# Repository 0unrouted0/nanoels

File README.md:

This software and instructions are [provided as is](LICENSE), without warranty of any kind.

See [the data of kachurovskiy](https://github.com/kachurovskiy/nanoels/) for the original NanoEls

# NanoEls H4 revised1 (currently unfinished work!!)
* This is an idea of an low cost variant with multiple placement and handsolder types for the components. For e.g.
    * PCB double sided 100mm x 100mm standard type
    * Design with free KiCad 8
    * All parts for hand solder (TCA8418 tricky, but possible - or usage of Adafruit Module)
    * One PCB for keypad and controls
    * Powering over USB or step-down converter with screw terminals
    * Interfacing to LCD via I2C interface over 4 pins possible (== same LCD type with I2C backpack PCB as sold on Aliexpress)
    * USB program and serial interface variants FT232RL or CH340 series
    * USB Connectors 90° types in two sides (idea: back connector>power, front connector>PC-control) or side entry both over 180° Types
    * ESP32-S3-WROOM-1 also possible (with antenna), currently used N16R8

* What's working in Hardware (with modified software)?
	* WARNING: This special hardware version is not checked against EMC, CE, FCC and so on...
    * Display over I2C Interface
    * Programming and serial interface over FT232RL for the ESP32-S3-WROOM-1 (N16R8)
    * Keypad with direct soldered Keypad controller

* What's working in Software?
    * Software should be (i can not test it) compatible with the original NanoEls H4
    * Software working with ardunio Espressive ESP32 3.0.1 boards package (based on ESP-IDF v5.1.4). Maybe NOT backwards compatible to 2.x.
    * Display in I2C mode working. Faultless together with secondary I2C channel for keypad interface. 
    * Added LiquidCrystal_I2C_pt for handling of two I2C interfaces an changeable pins, because there are no available Arduino libraries with I2C pointer parameter.
    * Currently not completely tested, but encoder detects something. Hardware timer for ASYNC and A1 mode maybe not 100% working (unclear).

* ToDo's and current bugs
    * More testing of HW and SW
    * Integration in a real lathe
    * Making a low cost 3d-printable housing
    * PCB: Pitch of buzzer is false for the delivered type. Maybe a dual pitch package is sensible
    * PCB: Through hole pad for thermal connection of ESP32 module should have a bigger size free of solder mask
    * PCB: maybe dual package in standard sizes for buzzer free wheeling diode
    * PCB: upload the latest version

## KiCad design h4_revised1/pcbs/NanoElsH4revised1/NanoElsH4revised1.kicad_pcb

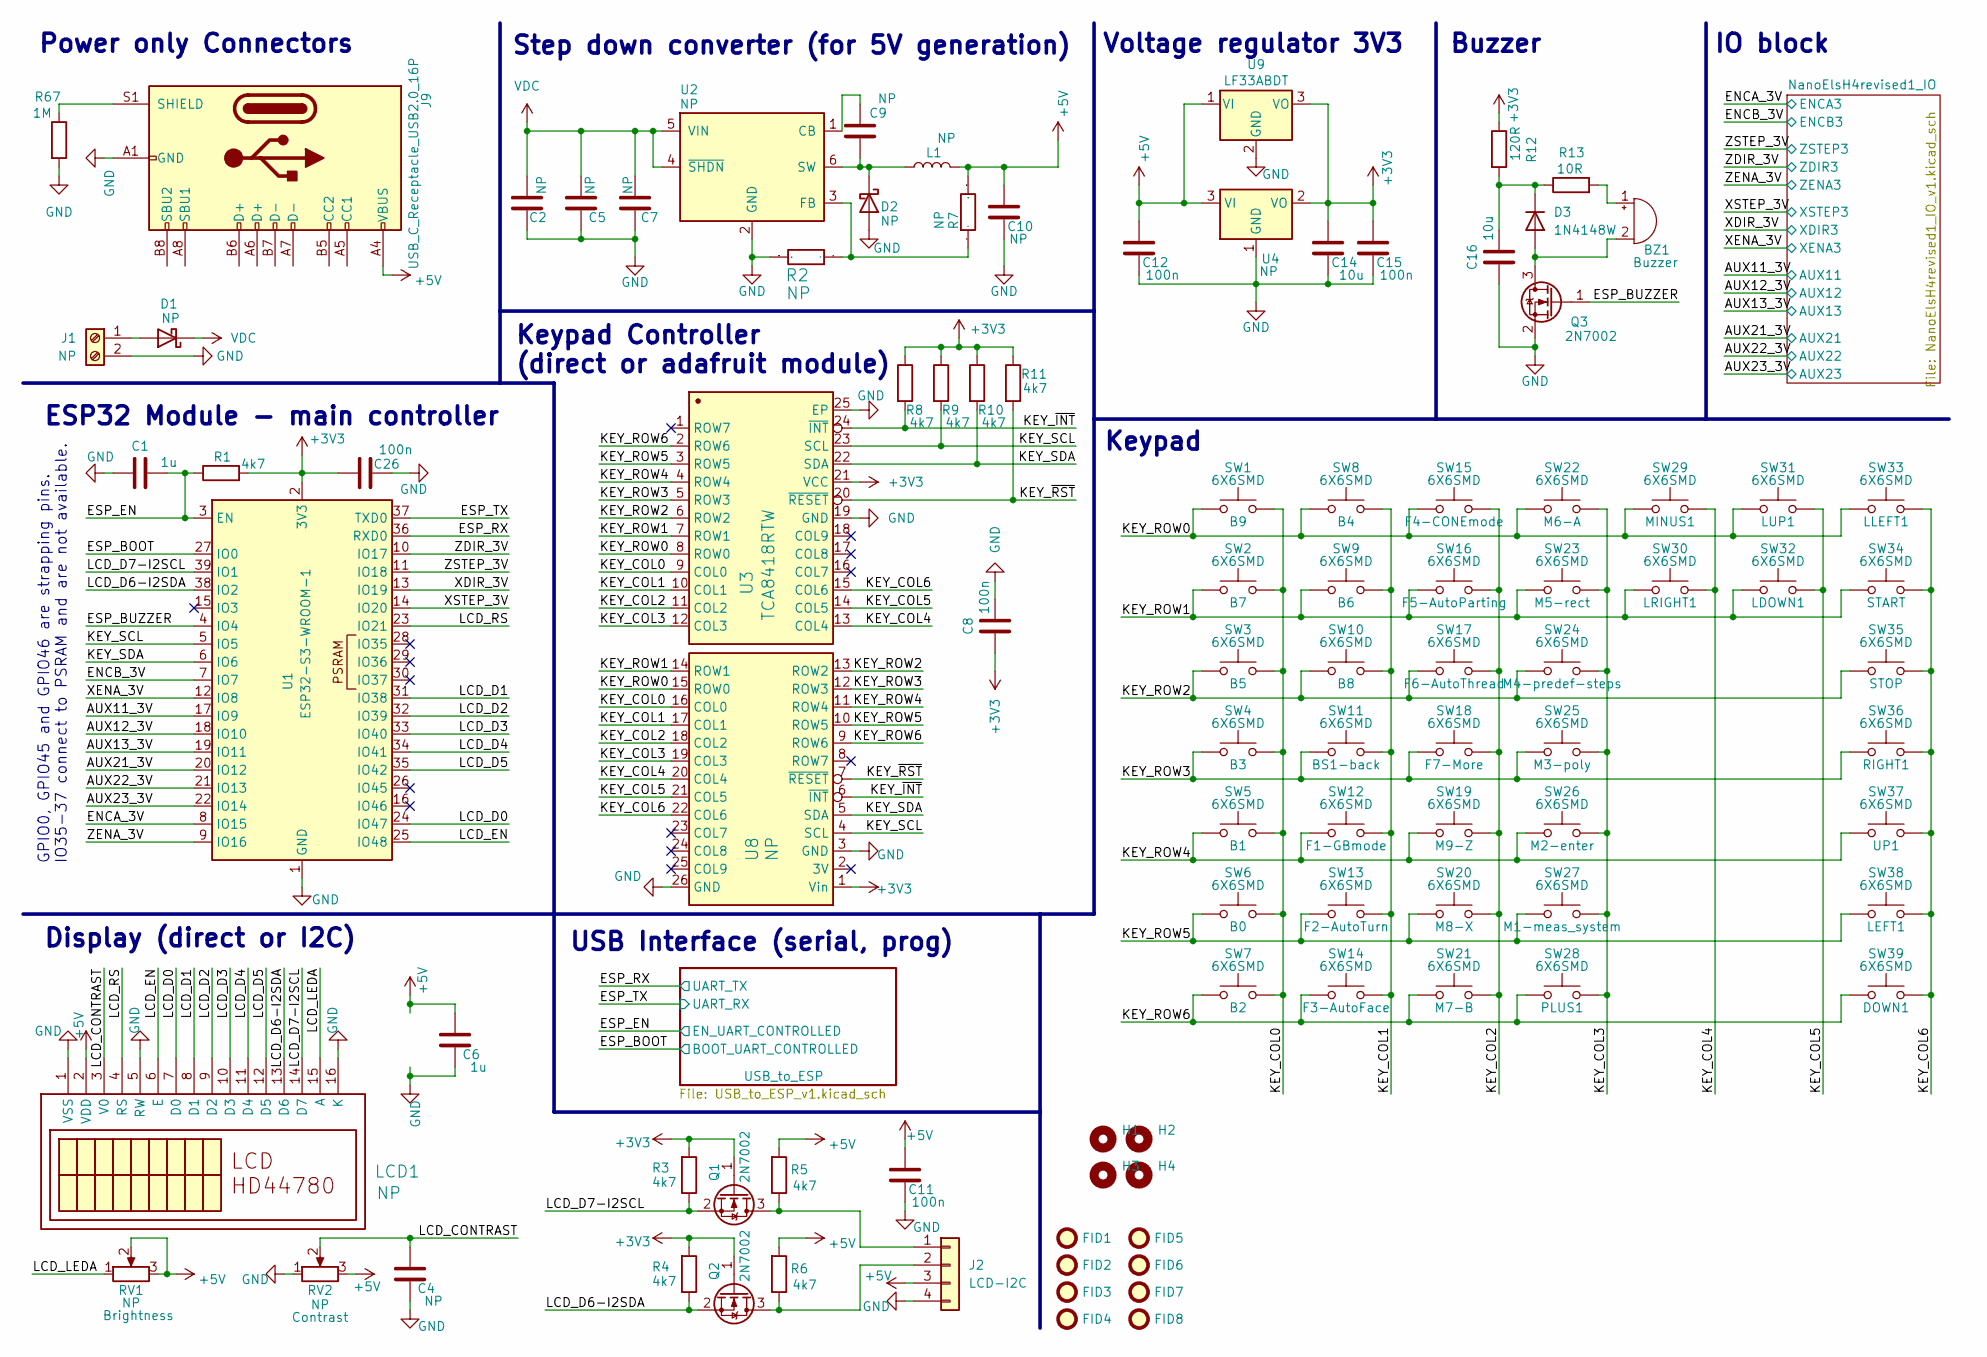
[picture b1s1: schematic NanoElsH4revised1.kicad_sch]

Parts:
BZ1: Buzzer; MagneticBuzzer_PUI_AT-0927-TT-6-R
C1, C6: 1u; C_0603_1608Metric
C2, C5: NP; C_1210_3225Metric
C4, C7, C9: NP; C_0603_1608Metric
C8, C11, C12, C15, C26: 100n; C_0603_1608Metric
C10: NP; C_1206_3216Metric
C14, C16: 10u; C_1206_3216Metric
D1, D2: NP; D_SMA
D3: 1N4148W; D_SOD-323
FID1, FID2, FID3, FID4, FID5, FID6, FID7, FID8: Fiducial_1.5mm_Mask3mm
H1, H2, H3, H4: MountingHole_3.2mm_M3
J1: NP; PhoenixContact_MCV_1,5_2-G-3.5_1x02_P3.50mm_Vertical
J2: LCD-I2C; PinHeader_1x04_P2.54mm_Horizontal
J9: USB_C_Receptacle_USB2.0_16P; USB_C_HorVert_topbot_GCT-JAE-HRO_USB4160-DX07S024WJ3R400-C3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
L1: NP; L_TDK_VLS6045EX_VLS6045AF
LCD1: NP; LCD_HD44780_header_horizontal
Q1, Q2, Q3: 2N7002; SOT-23
R1, R3, R4, R5, R6, R8, R9, R10, R11: 4k7; R_0603_1608Metric
R2, R7: NP; R_0603_1608Metric
R12: 120R; R_0603_1608Metric
R13: 10R; R_0603_1608Metric
R67: 1M; R_0603_1608Metric
RV1, RV2: NP; Potentiometer_ACP_CA6-VSMD_Vertical
SW1, SW2, SW3, SW4, SW5, SW6, SW7, SW8, SW9, SW10, SW11, SW12, SW13, SW14, SW15, SW16, SW17, SW18, SW19, SW20, SW21, SW22, SW23, SW24, SW25, SW26, SW27, SW28, SW29, SW30, SW31, SW32, SW33, SW34, SW35, SW36, SW37, SW38, SW39: 6X6SMD; SW_Push_1P1T_NO_6x6mm_H9.5mm
U1: ESP32-S3-WROOM-1; ESP32-S3-WROOM-1_bighole
U2: NP; SOT-23-6
U3: TCA8418RTW; WQFN-24-1EP_4x4mm_P0.5mm_EP2.45x2.45mm
U4: NP; SOT-223-3_TabPin2
U8: NP; Adafruit_STEMMA_TCA8418
U9: LF33ABDT; TO-252-2

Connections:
+3V3: C8.1, C14.2, C15.2, C26.2, Q1.1 (G), Q2.1 (G), R1.2, R3.2, R4.2, R8.1, R9.1, R10.1, R11.1, R12.1, U1.2 (3V3), U3.21 (VCC), U4.2 (VO), U8.1 (Vin), U9.3 (VO); also elsewhere on the board
+5V: C6.2, C10.2, C11.2, C12.2, J2.3, J9.A4 (VBUS), J9.A9 (VBUS), J9.B4 (VBUS), J9.B9 (VBUS), L1.2, LCD1.2 (VDD), R5.2, R6.2, R7.1, RV1.2, RV1.3, RV2.3, U4.3 (VI), U9.1 (VI); also elsewhere on the board
/AUX11_3V: U1.17 (IO9); also elsewhere on the board
/AUX12_3V: U1.18 (IO10); also elsewhere on the board
/AUX13_3V: U1.19 (IO11); also elsewhere on the board
/AUX21_3V: U1.20 (IO12); also elsewhere on the board
/AUX22_3V: U1.21 (IO13); also elsewhere on the board
/AUX23_3V: U1.22 (IO14); also elsewhere on the board
/ENCA_3V: U1.8 (IO15); also elsewhere on the board
/ENCB_3V: U1.7 (IO7); also elsewhere on the board
/ESP_BOOT: U1.27 (IO0); also elsewhere on the board
/ESP_BUZZER: Q3.1 (G), U1.4 (IO4)
/ESP_EN: C1.2, R1.1, U1.3 (EN); also elsewhere on the board
/ESP_RX: U1.36 (RXD0); also elsewhere on the board
/ESP_TX: U1.37 (TXD0); also elsewhere on the board
/KEY_COL0: SW1.2, SW2.2, SW3.2, SW4.2, SW5.2, SW6.2, SW7.2, U3.9 (COL0), U8.16 (COL0)
/KEY_COL1: SW8.2, SW9.2, SW10.2, SW11.2, SW12.2, SW13.2, SW14.2, U3.10 (COL1), U8.17 (COL1)
/KEY_COL2: SW15.2, SW16.2, SW17.2, SW18.2, SW19.2, SW20.2, SW21.2, U3.11 (COL2), U8.18 (COL2)
/KEY_COL3: SW22.2, SW23.2, SW24.2, SW25.2, SW26.2, SW27.2, SW28.2, U3.12 (COL3), U8.19 (COL3)
/KEY_COL4: SW29.2, SW30.2, U3.13 (COL4), U8.20 (COL4)
/KEY_COL5: SW31.2, SW32.2, U3.14 (COL5), U8.21 (COL5)
/KEY_COL6: SW33.2, SW34.2, SW35.2, SW36.2, SW37.2, SW38.2, SW39.2, U3.15 (COL6), U8.22 (COL6)
/KEY_ROW0: SW1.1, SW8.1, SW15.1, SW22.1, SW29.1, SW31.1, SW33.1, U3.8 (ROW0), U8.15 (ROW0)
/KEY_ROW1: SW2.1, SW9.1, SW16.1, SW23.1, SW30.1, SW32.1, SW34.1, U3.7 (ROW1), U8.14 (ROW1)
/KEY_ROW2: SW3.1, SW10.1, SW17.1, SW24.1, SW35.1, U3.6 (ROW2), U8.13 (ROW2)
/KEY_ROW3: SW4.1, SW11.1, SW18.1, SW25.1, SW36.1, U3.5 (ROW3), U8.12 (ROW3)
/KEY_ROW4: SW5.1, SW12.1, SW19.1, SW26.1, SW37.1, U3.4 (ROW4), U8.11 (ROW4)
/KEY_ROW5: SW6.1, SW13.1, SW20.1, SW27.1, SW38.1, U3.3 (ROW5), U8.10 (ROW5)
/KEY_ROW6: SW7.1, SW14.1, SW21.1, SW28.1, SW39.1, U3.2 (ROW6), U8.9 (ROW6)
/KEY_SCL: R9.2, U1.5 (IO5), U3.23 (SCL), U8.4 (SCL)
/KEY_SDA: R10.2, U1.6 (IO6), U3.22 (SDA), U8.5 (SDA)
/KEY_~INT: R8.2, U3.24 (~INT), U8.6 (~INT)
/KEY_~RST: R11.2, U3.20 (~RESET), U8.7 (~RESET)
/LCD_CONTRAST: C4.2, LCD1.3 (V0), RV2.2
/LCD_D0: LCD1.7 (D0), U1.24 (IO47)
/LCD_D1: LCD1.8 (D1), U1.31 (IO38)
/LCD_D2: LCD1.9 (D2), U1.32 (IO39)
/LCD_D3: LCD1.10 (D3), U1.33 (IO40)
/LCD_D4: LCD1.11 (D4), U1.34 (IO41)
/LCD_D5: LCD1.12 (D5), U1.35 (IO42)
/LCD_D6-I2SDA: LCD1.13 (D6), Q2.2 (S), R4.1, U1.38 (IO2)
/LCD_D7-I2SCL: LCD1.14 (D7), Q1.2 (S), R3.1, U1.39 (IO1)
/LCD_EN: LCD1.6 (E), U1.25 (IO48)
/LCD_LEDA: LCD1.15 (A), RV1.1
/LCD_RS: LCD1.4 (RS), U1.23 (IO21)
/XDIR_3V: U1.13 (IO19); also elsewhere on the board
/XENA_3V: U1.12 (IO8); also elsewhere on the board
/XSTEP_3V: U1.14 (IO20); also elsewhere on the board
/ZDIR_3V: U1.10 (IO17); also elsewhere on the board
/ZENA_3V: U1.9 (IO16); also elsewhere on the board
/ZSTEP_3V: U1.11 (IO18); also elsewhere on the board
GND: C1.1, C2.1, C4.1, C5.1, C6.1, C7.1, C8.2, C10.1, C11.1, C12.1, C14.1, C15.1, C16.1, C26.1, D2.2 (A), J1.2, J2.4, J9.A1 (GND), J9.A12 (GND), J9.B1 (GND), J9.B12 (GND), LCD1.1 (VSS), LCD1.5 (RW), LCD1.16 (K), Q3.2 (S), R2.1, R67.2, RV2.1, U1.1 (GND), U1.40 (GND), U1.41 (GND), U2.2 (GND), U3.19 (GND), U3.25 (EP), U4.1 (GND), U8.3 (GND), U8.26 (GND), U9.2 (GND); also elsewhere on the board
unnamed: BZ1.1 (+), R13.2
unnamed: BZ1.2 (-), D3.2 (A), Q3.3 (D)
unnamed: D1.2 (A), J1.1
unnamed: C9.1, D2.1 (K), L1.1, U2.6 (SW)
unnamed: C16.2, D3.1 (K), R12.2, R13.1
unnamed: J2.1, Q1.3 (D), R5.1
unnamed: J2.2, Q2.3 (D), R6.1
unnamed: J9.S1 (SHIELD), R67.1
unnamed: C9.2, U2.1 (CB)
unnamed: R2.2, R7.2, U2.3 (FB)
VDC: C2.2, C5.2, C7.2, D1.1 (K), U2.4 (~SHDN), U2.5 (VIN)

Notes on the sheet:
USB Interface (serial, prog)
Step down converter (for 5V generation)
Keypad Controller (direct or adafruit module)
GPIO0, GPIO45 and GPIO46 are strapping pins. IO35-37 connect to PSRAM and are not available.
Keypad
ESP32 Module - main controller
Power only Connectors
Buzzer
Display (direct or I2C)
Voltage regulator 3V3
IO block

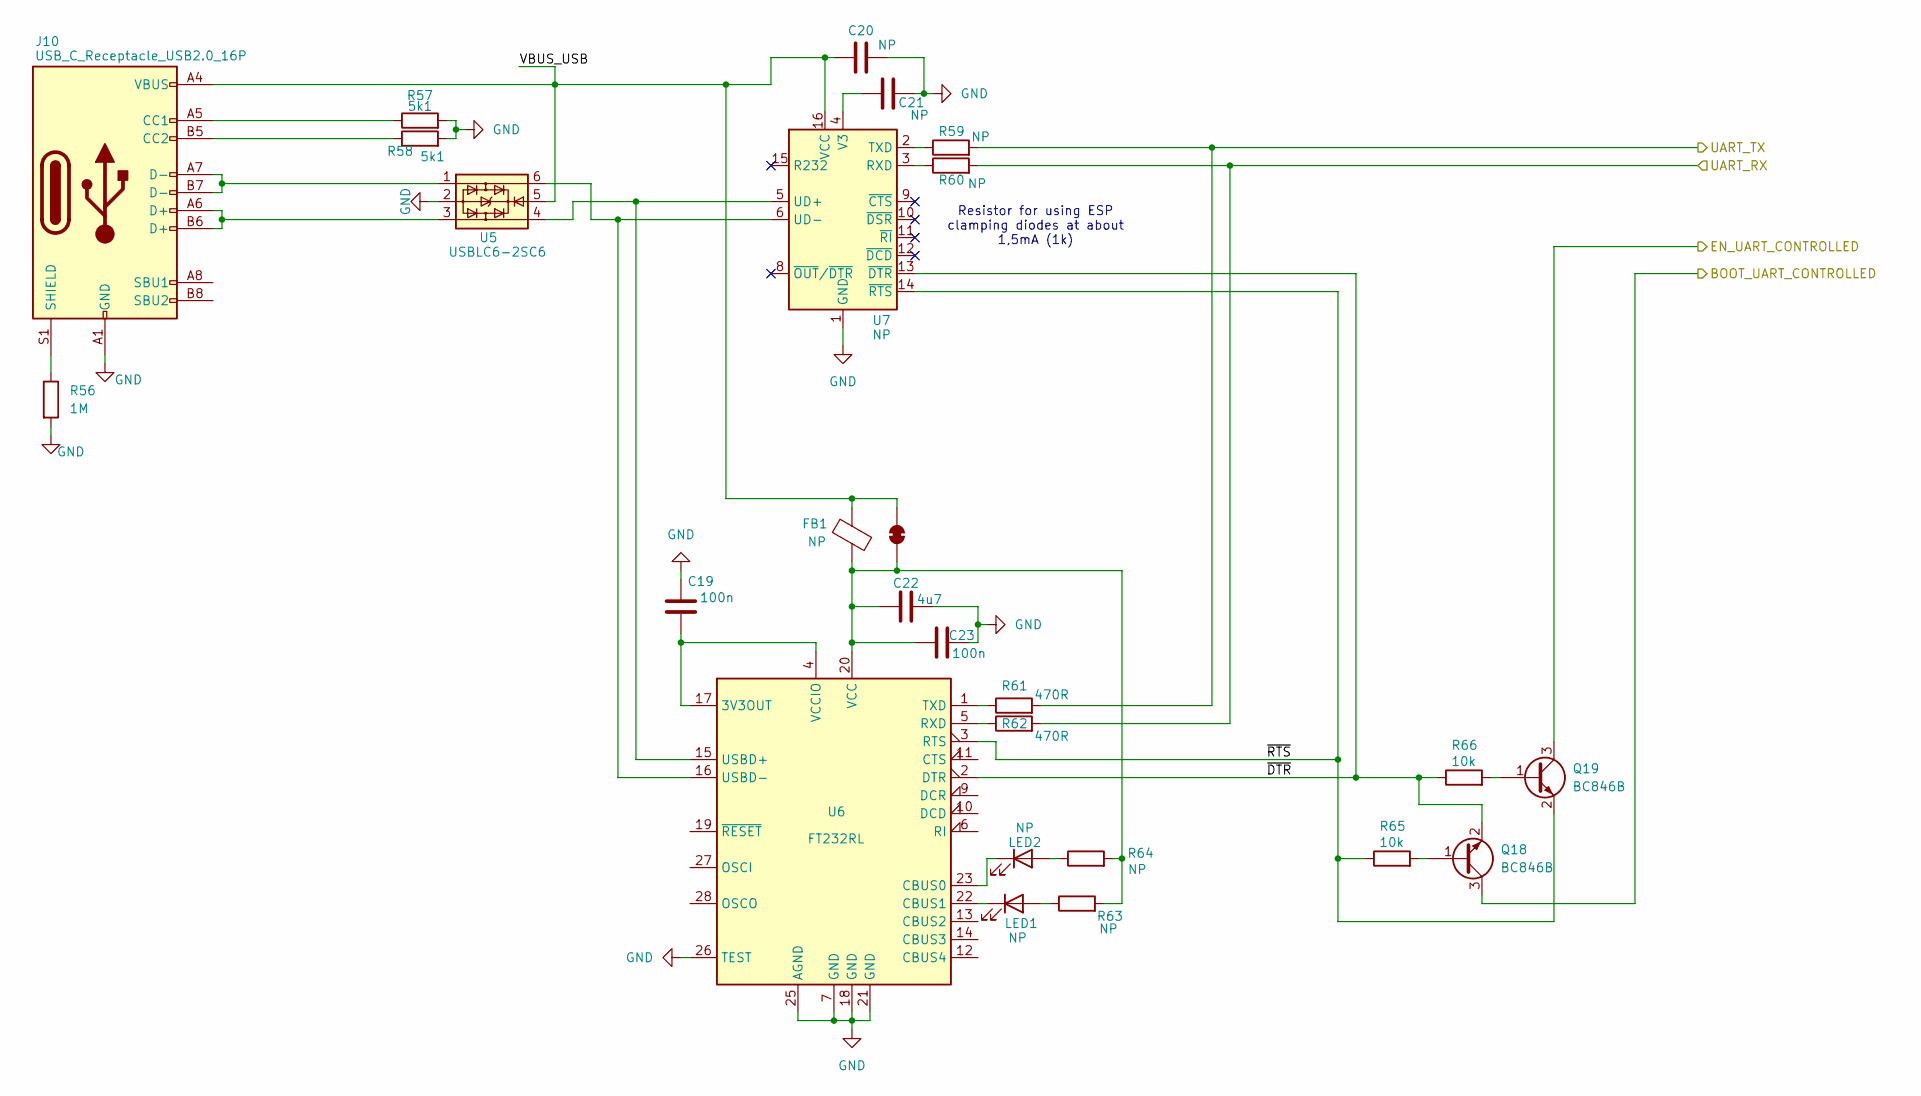
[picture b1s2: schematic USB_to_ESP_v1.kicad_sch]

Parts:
C19, C23: 100n; C_0603_1608Metric
C20, C21: NP; C_0603_1608Metric
C22: 4u7; C_1206_3216Metric
FB1: NP; L_0603_1608Metric
J10: USB_C_Receptacle_USB2.0_16P; USB_C_HorVert_top_GCT-JAE-HRO_USB4160-DX07S024WJ3R400-C31M12
JP1: R_0603_1608Metric_shorted
LED1, LED2: NP; LED_0603_1608Metric
Q18, Q19: BC846B; SOT-23
R56: 1M; R_0603_1608Metric
R57, R58: 5k1; R_0603_1608Metric
R59, R60, R63, R64: NP; R_0603_1608Metric
R61, R62: 470R; R_0603_1608Metric
R65, R66: 10k; R_0603_1608Metric
U5: USBLC6-2SC6; SOT-23-6
U6: FT232RL; SSOP-28_5.3x10.2mm_P0.65mm
U7: NP; SOIC-16_3.9x9.9mm_P1.27mm

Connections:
/ESP_BOOT: Q18.3 (C); also elsewhere on the board
/ESP_EN: Q19.3 (C); also elsewhere on the board
/ESP_RX: R59.2, R61.2; also elsewhere on the board
/ESP_TX: R60.2, R62.2; also elsewhere on the board
/USB_to_ESP/VBUS_USB: C20.1, FB1.2, J10.A4 (VBUS), J10.A9 (VBUS), J10.B4 (VBUS), J10.B9 (VBUS), JP1.2 (B), U5.5, U7.16 (VCC)
/USB_to_ESP/~DTR: Q18.2 (E), R66.1, U6.2 (DTR), U7.13 (~DTR)
/USB_to_ESP/~RTS: Q19.2 (E), R65.1, U6.3 (RTS), U7.14 (~RTS)
GND: C19.2, C20.2, C21.2, C22.1, C23.1, J10.A1 (GND), J10.A12 (GND), J10.B1 (GND), J10.B12 (GND), R56.2, R57.2, R58.2, U5.2, U6.7 (GND), U6.18 (GND), U6.21 (GND), U6.25 (AGND), U6.26 (TEST), U7.1 (GND); also elsewhere on the board
unnamed: J10.A5 (CC1), R57.1
unnamed: J10.B5 (CC2), R58.1
unnamed: J10.A6 (D+), J10.B6 (D+), U5.3
unnamed: J10.A7 (D-), J10.B7 (D-), U5.1
unnamed: J10.S1 (SHIELD), R56.1
unnamed: C22.2, C23.2, FB1.1, JP1.1 (A), R63.2, R64.2, U6.20 (VCC)
unnamed: LED1.2 (A), R63.1
unnamed: LED1.1 (K), U6.22 (CBUS1)
unnamed: LED2.2 (A), R64.1
unnamed: LED2.1 (K), U6.23 (CBUS0)
unnamed: Q18.1 (B), R65.2
unnamed: Q19.1 (B), R66.2
unnamed: C19.1, U6.4 (VCCIO), U6.17 (3V3OUT)
unnamed: R62.1, U6.5 (RXD)
unnamed: R61.1, U6.1 (TXD)
unnamed: U5.4, U6.15 (USBD+), U7.5 (UD+)
unnamed: U5.6, U6.16 (USBD-), U7.6 (UD-)
unnamed: R60.1, U7.3 (RXD)
unnamed: R59.1, U7.2 (TXD)
unnamed: C21.1, U7.4 (V3)

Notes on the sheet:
Resistor for using ESP clamping diodes at about 1,5mA (1k)

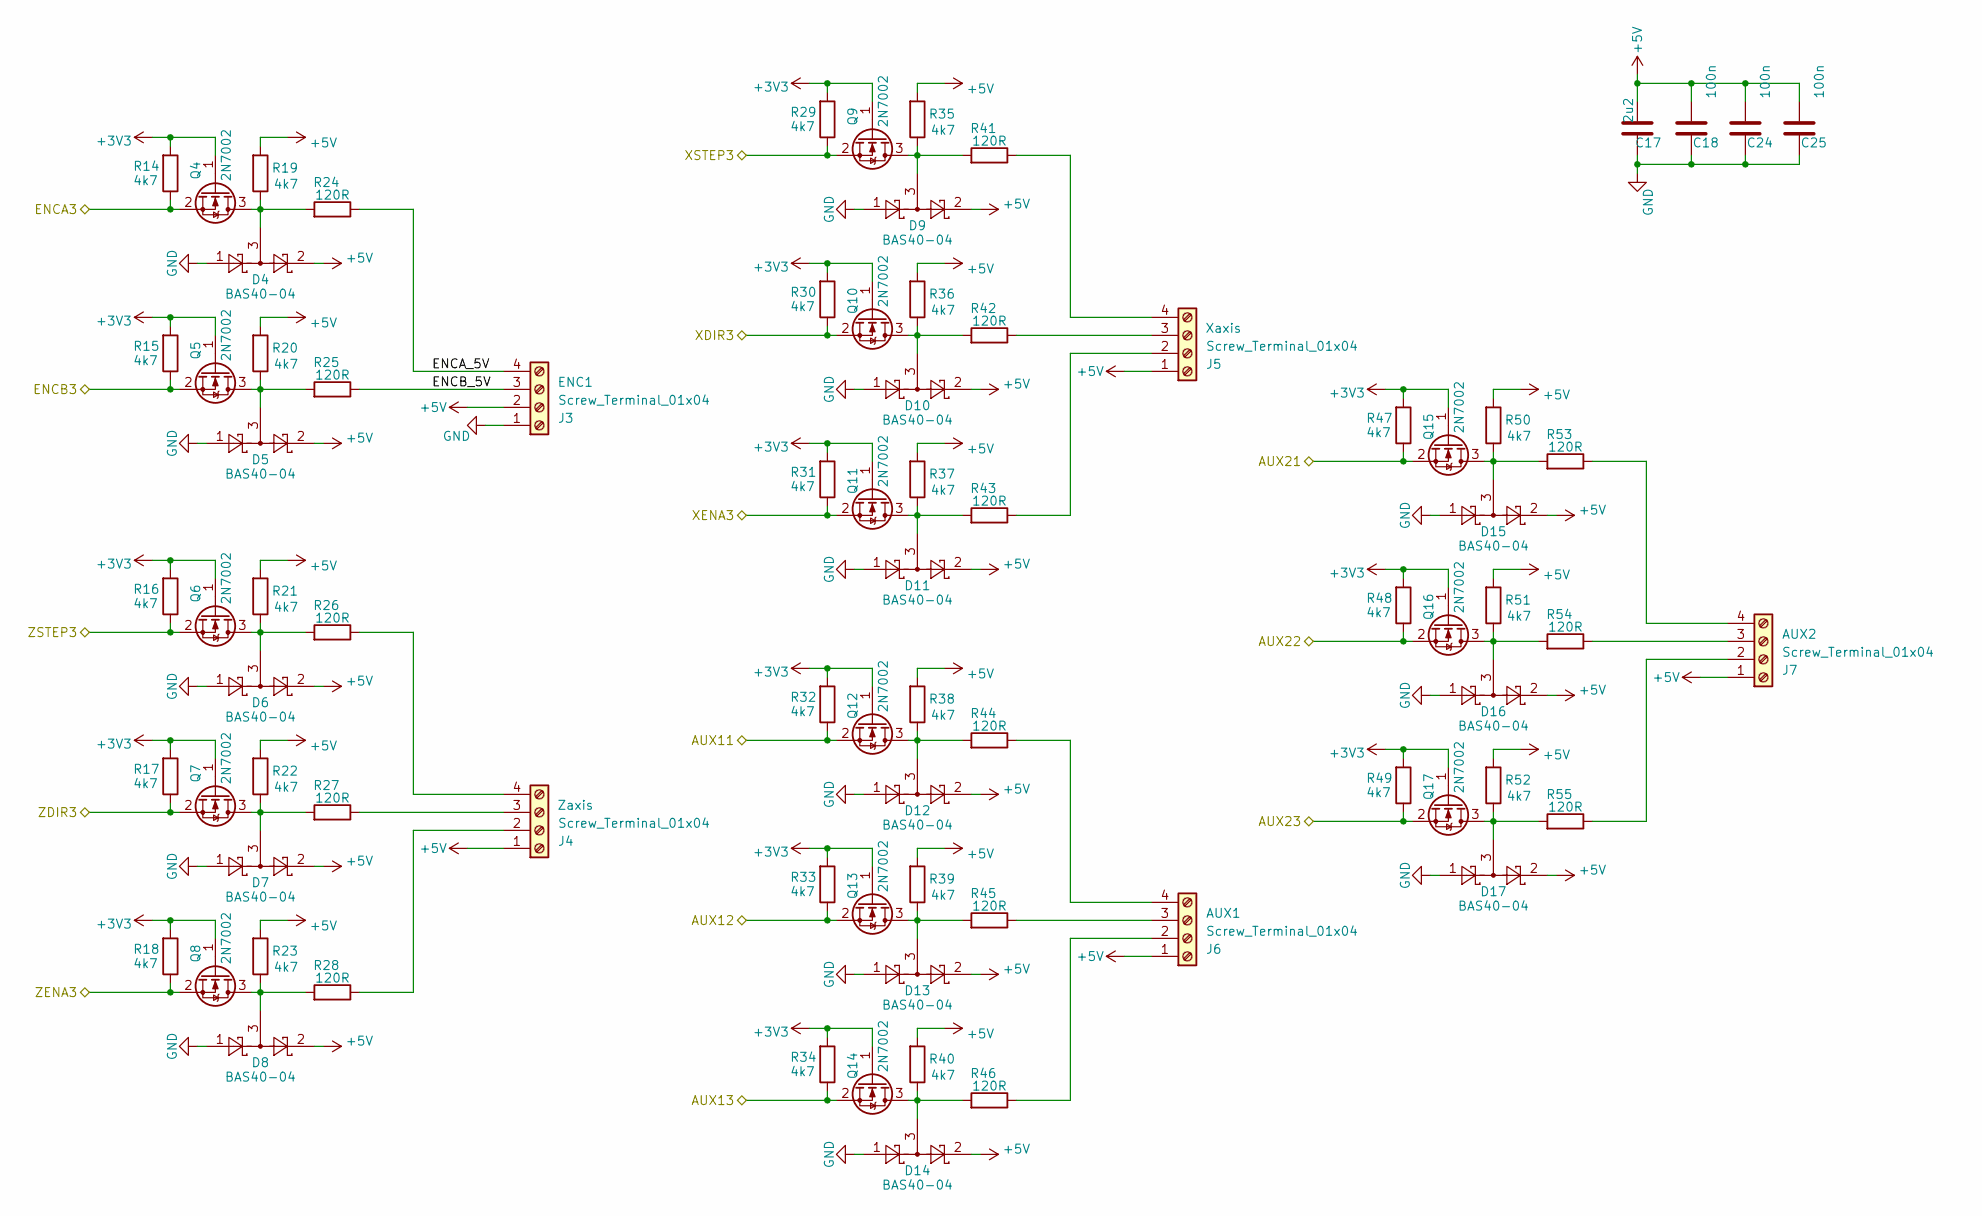
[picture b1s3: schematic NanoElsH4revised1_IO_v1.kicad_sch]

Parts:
C17: 2u2; C_1206_3216Metric
C18, C24, C25: 100n; C_0603_1608Metric
D4, D5, D6, D7, D8, D9, D10, D11, D12, D13, D14, D15, D16, D17: BAS40-04; SOT-23
J3, J4, J5, J6, J7: Screw_Terminal_01x04; PhoenixContact_MCV_1,5_4-G-3.5_1x04_P3.50mm_Vertical
Q4, Q5, Q6, Q7, Q8, Q9, Q10, Q11, Q12, Q13, Q14, Q15, Q16, Q17: 2N7002; SOT-23
R14, R15, R16, R17, R18, R19, R20, R21, R22, R23, R29, R30, R31, R32, R33, R34, R35, R36, R37, R38, R39, R40, R47, R48, R49, R50, R51, R52: 4k7; R_0603_1608Metric
R24, R25, R26, R27, R28, R41, R42, R43, R44, R45, R46, R53, R54, R55: 120R; R_0603_1608Metric

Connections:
+3V3: Q4.1 (G), Q5.1 (G), Q6.1 (G), Q7.1 (G), Q8.1 (G), Q9.1 (G), Q10.1 (G), Q11.1 (G), Q12.1 (G), Q13.1 (G), Q14.1 (G), Q15.1 (G), Q16.1 (G), Q17.1 (G), R14.2, R15.2, R16.2, R17.2, R18.2, R29.2, R30.2, R31.2, R32.2, R33.2, R34.2, R47.2, R48.2, R49.2; also elsewhere on the board
+5V: C17.2, C18.2, C24.2, C25.2, D4.2, D5.2, D6.2, D7.2, D8.2, D9.2, D10.2, D11.2, D12.2, D13.2, D14.2, D15.2, D16.2, D17.2, J3.2, J4.1, J5.1, J6.1, J7.1, R19.2, R20.2, R21.2, R22.2, R23.2, R35.2, R36.2, R37.2, R38.2, R39.2, R40.2, R50.2, R51.2, R52.2; also elsewhere on the board
/AUX11_3V: Q12.2 (S), R32.1; also elsewhere on the board
/AUX12_3V: Q13.2 (S), R33.1; also elsewhere on the board
/AUX13_3V: Q14.2 (S), R34.1; also elsewhere on the board
/AUX21_3V: Q15.2 (S), R47.1; also elsewhere on the board
/AUX22_3V: Q16.2 (S), R48.1; also elsewhere on the board
/AUX23_3V: Q17.2 (S), R49.1; also elsewhere on the board
/ENCA_3V: Q4.2 (S), R14.1; also elsewhere on the board
/ENCB_3V: Q5.2 (S), R15.1; also elsewhere on the board
/NanoElsH4revised1_IO/ENCA_5V: J3.4, R24.1
/NanoElsH4revised1_IO/ENCB_5V: J3.3, R25.1
/XDIR_3V: Q10.2 (S), R30.1; also elsewhere on the board
/XENA_3V: Q11.2 (S), R31.1; also elsewhere on the board
/XSTEP_3V: Q9.2 (S), R29.1; also elsewhere on the board
/ZDIR_3V: Q7.2 (S), R17.1; also elsewhere on the board
/ZENA_3V: Q8.2 (S), R18.1; also elsewhere on the board
/ZSTEP_3V: Q6.2 (S), R16.1; also elsewhere on the board
GND: C17.1, C18.1, C24.1, C25.1, D4.1, D5.1, D6.1, D7.1, D8.1, D9.1, D10.1, D11.1, D12.1, D13.1, D14.1, D15.1, D16.1, D17.1, J3.1; also elsewhere on the board
unnamed: J4.2, R28.1
unnamed: J4.3, R27.1
unnamed: J4.4, R26.1
unnamed: J5.2, R43.1
unnamed: J5.3, R42.1
unnamed: J5.4, R41.1
unnamed: J6.2, R46.1
unnamed: J6.3, R45.1
unnamed: J6.4, R44.1
unnamed: J7.2, R55.1
unnamed: J7.3, R54.1
unnamed: J7.4, R53.1
unnamed: D4.3, Q4.3 (D), R19.1, R24.2
unnamed: D5.3, Q5.3 (D), R20.1, R25.2
unnamed: D6.3, Q6.3 (D), R21.1, R26.2
unnamed: D7.3, Q7.3 (D), R22.1, R27.2
unnamed: D8.3, Q8.3 (D), R23.1, R28.2
unnamed: D9.3, Q9.3 (D), R35.1, R41.2
unnamed: D10.3, Q10.3 (D), R36.1, R42.2
unnamed: D11.3, Q11.3 (D), R37.1, R43.2
unnamed: D12.3, Q12.3 (D), R38.1, R44.2
unnamed: D13.3, Q13.3 (D), R39.1, R45.2
unnamed: D14.3, Q14.3 (D), R40.1, R46.2
unnamed: D15.3, Q15.3 (D), R50.1, R53.2
unnamed: D16.3, Q16.3 (D), R51.1, R54.2
unnamed: D17.3, Q17.3 (D), R52.1, R55.2

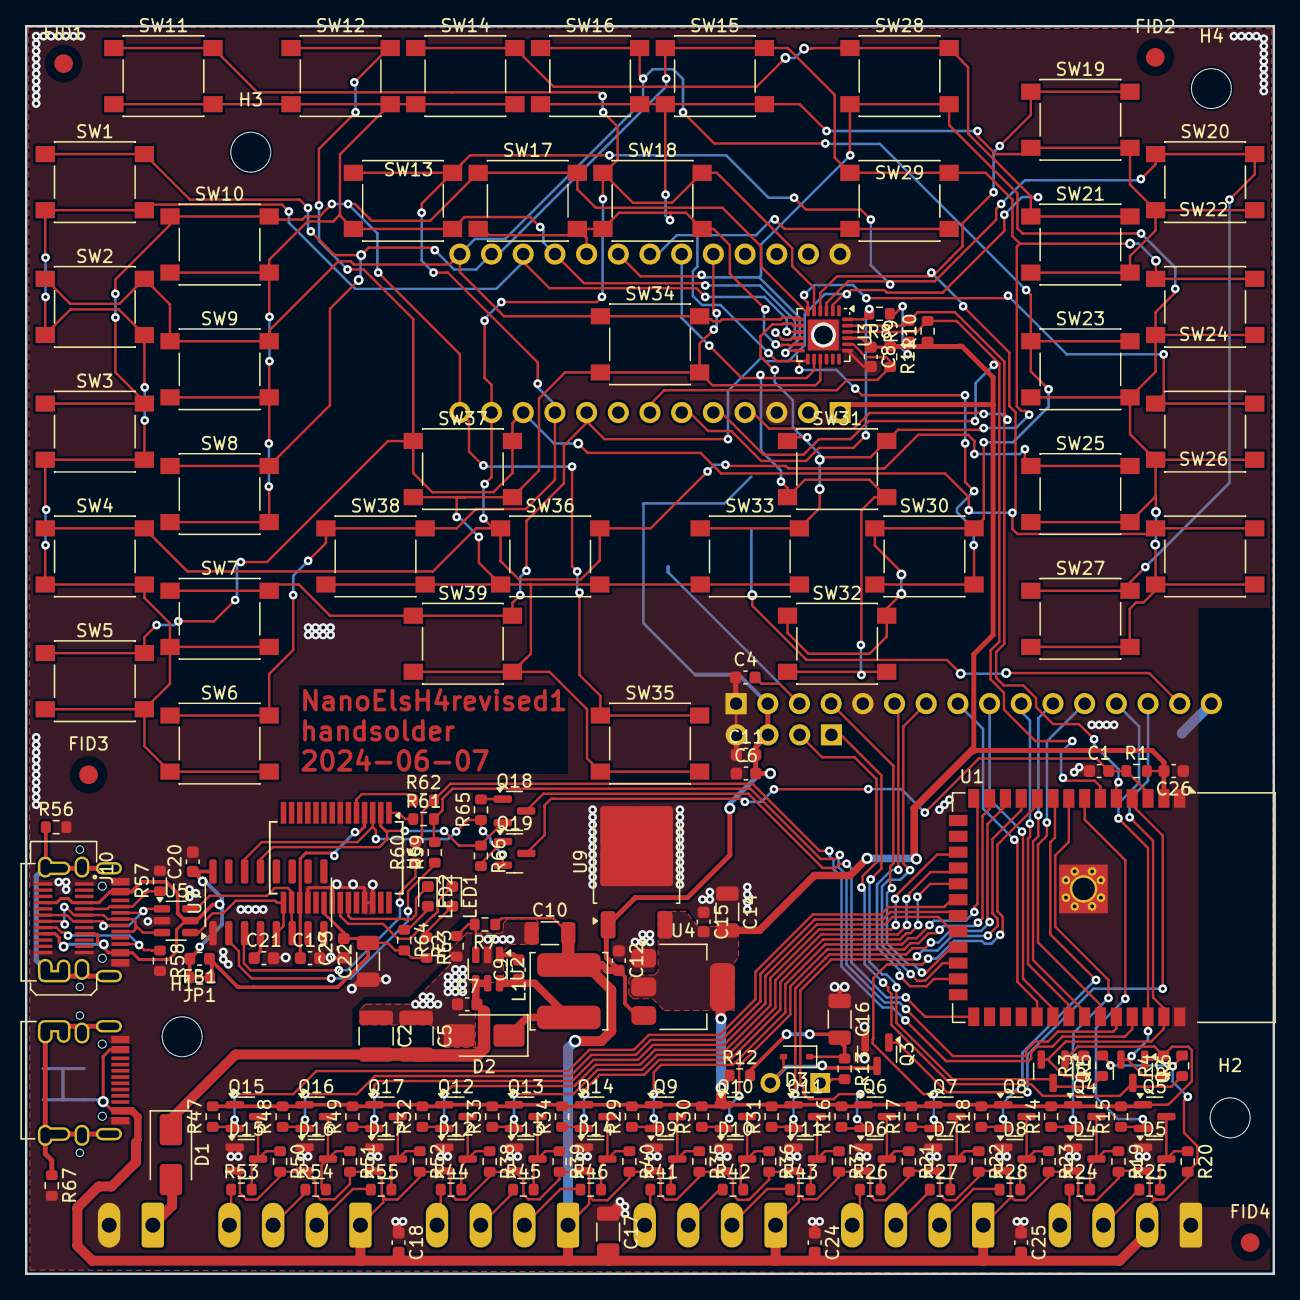
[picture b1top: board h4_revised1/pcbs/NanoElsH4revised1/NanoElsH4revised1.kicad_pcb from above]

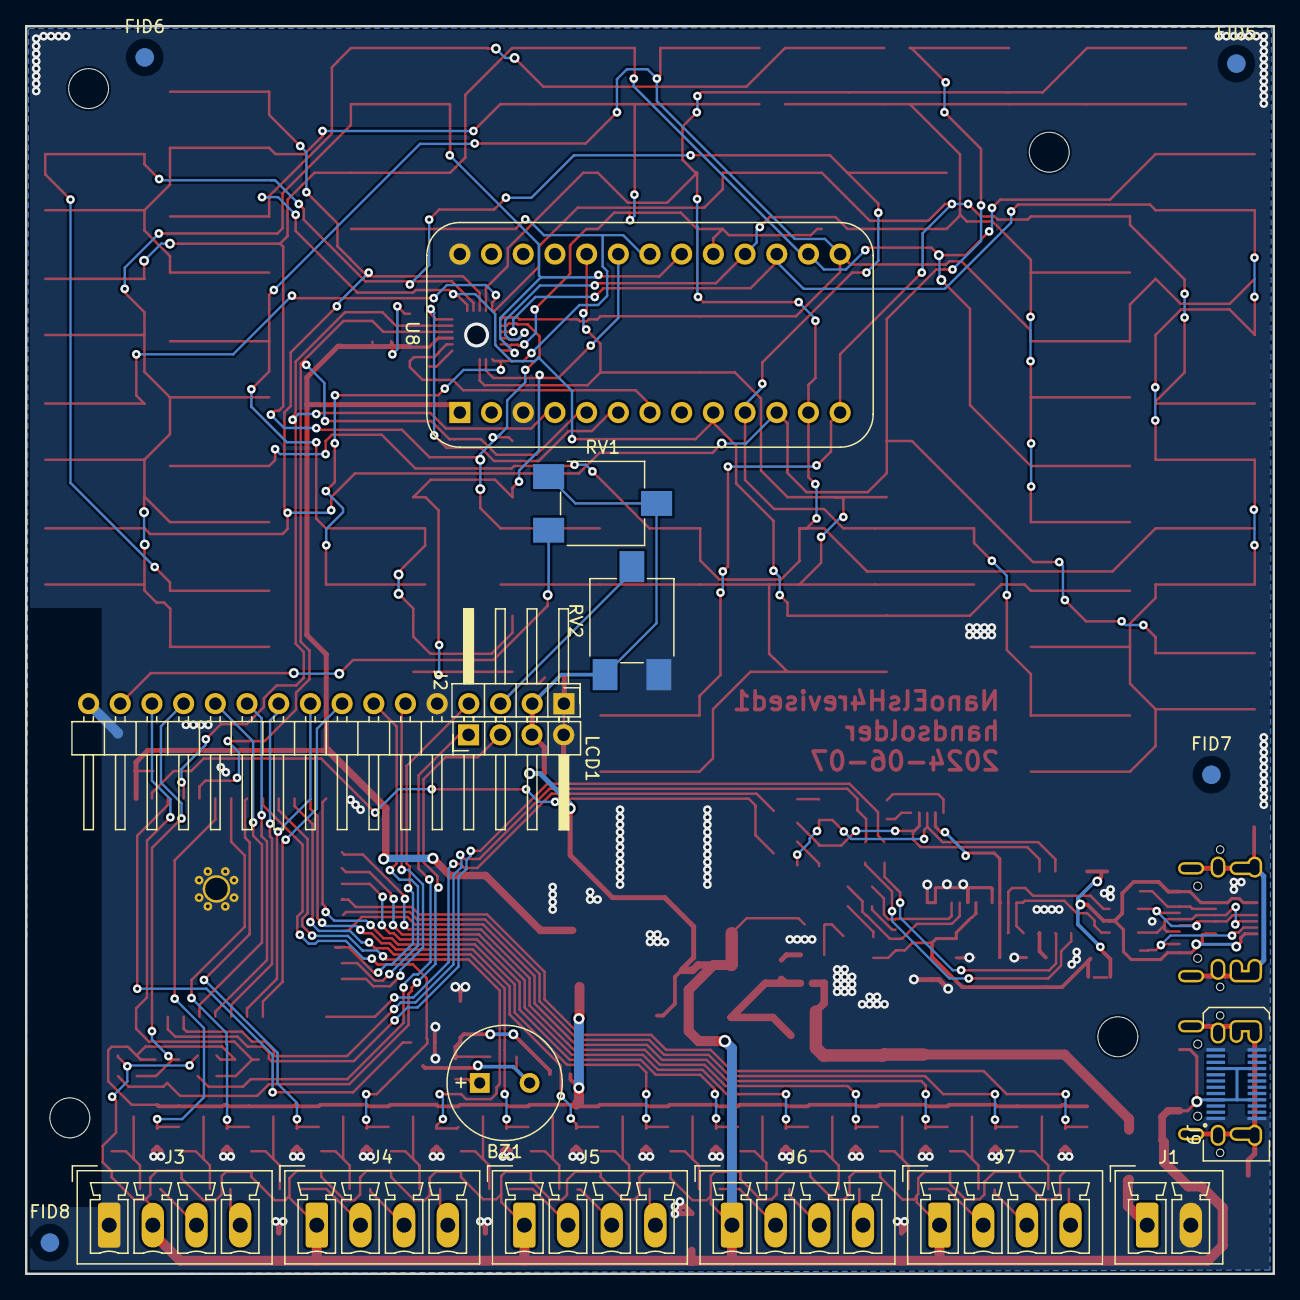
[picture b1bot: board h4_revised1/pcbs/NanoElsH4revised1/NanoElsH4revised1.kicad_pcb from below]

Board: 2 copper layers, 100.0 x 100.0 mm, 205 parts (17 on the bottom side), 114 nets.

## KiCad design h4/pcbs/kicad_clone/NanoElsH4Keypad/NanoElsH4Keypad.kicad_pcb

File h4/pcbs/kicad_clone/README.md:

- imported easyeda projects directly with KiCad 8.0.2 and saved files
- seems OK, but not tested for importing failures

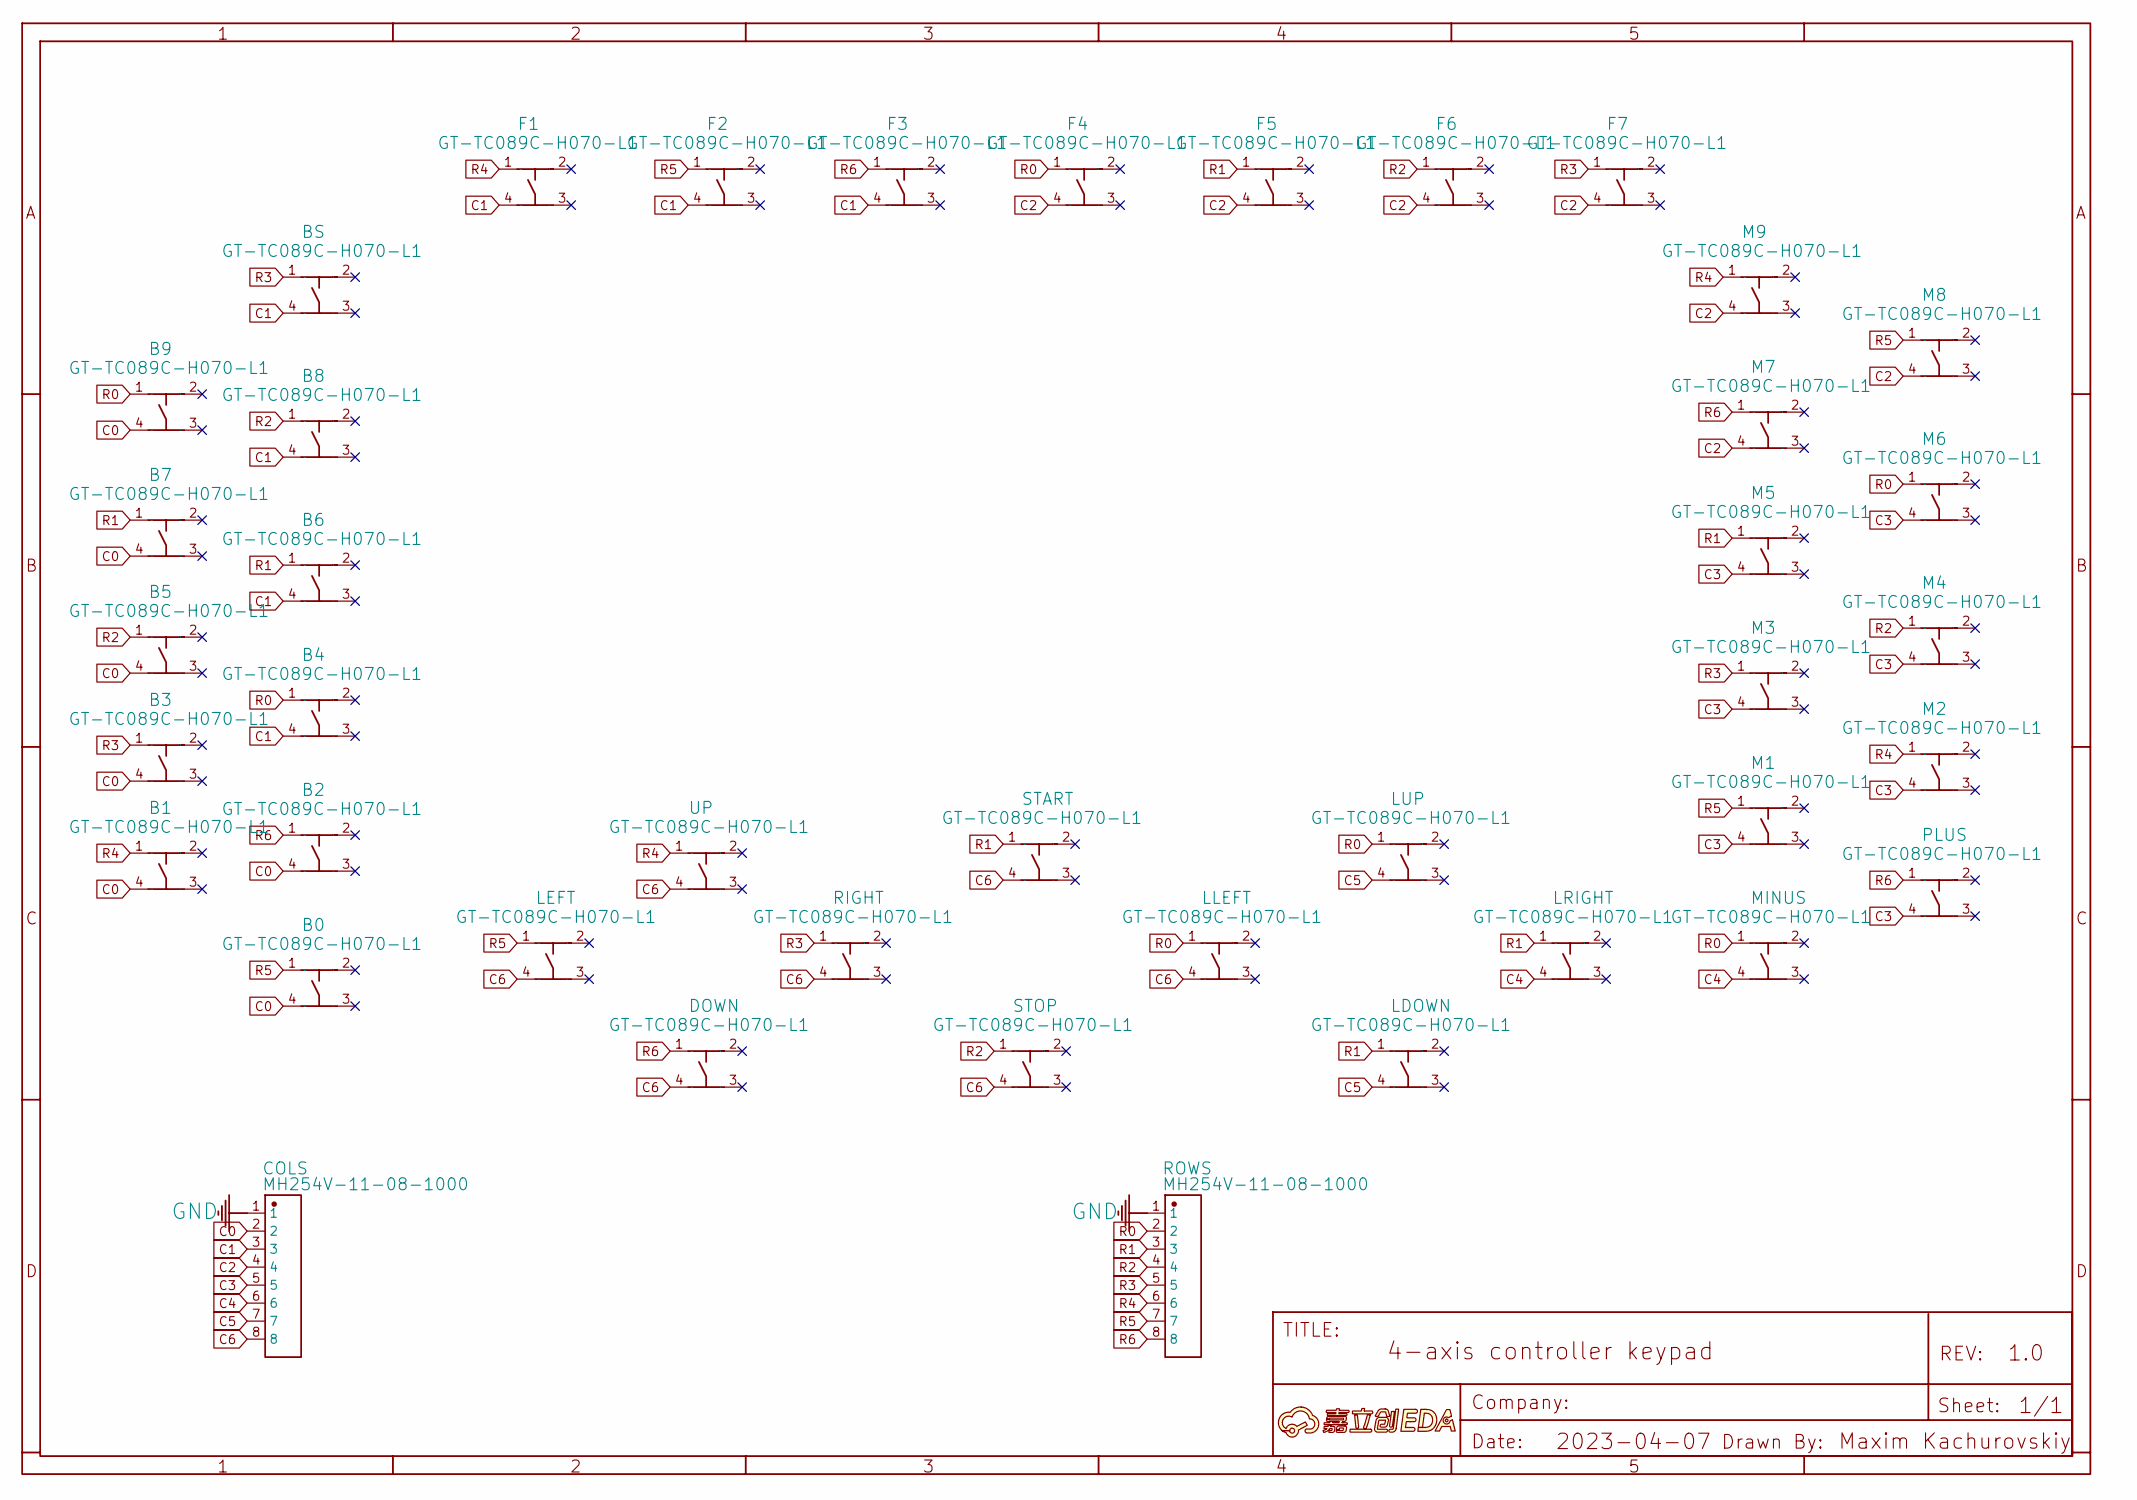
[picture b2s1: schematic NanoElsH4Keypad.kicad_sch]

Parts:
A: A
B0, B1, B2, B3, B4, B5, B6, B7, B8, B9: GT-TC089C-H070-L1
BS: GT-TC089C-H070-L1
COLS: MH254V-11-08-1000
DOWN: GT-TC089C-H070-L1
F1, F2, F3, F4, F5, F6, F7: GT-TC089C-H070-L1
LDOWN: GT-TC089C-H070-L1
LEFT: GT-TC089C-H070-L1
LLEFT: GT-TC089C-H070-L1
LRIGHT: GT-TC089C-H070-L1
LUP: GT-TC089C-H070-L1
M1, M2, M3, M4, M5, M6, M7, M8, M9: GT-TC089C-H070-L1
MINUS: GT-TC089C-H070-L1
PLUS: GT-TC089C-H070-L1
RIGHT: GT-TC089C-H070-L1
ROWS: MH254V-11-08-1000
START: GT-TC089C-H070-L1
STOP: GT-TC089C-H070-L1
UP: GT-TC089C-H070-L1

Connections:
C0: B0.4, B1.4, B2.4, B3.4, B5.4, B7.4, B9.4, COLS.2
C1: B4.4, B6.4, B8.4, BS.4, COLS.3, F1.4, F2.4, F3.4
C2: COLS.4, F4.4, F5.4, F6.4, F7.4, M7.4, M8.4, M9.4
C3: COLS.5, M1.4, M2.4, M3.4, M4.4, M5.4, M6.4, PLUS.4
C4: COLS.6, LRIGHT.4, MINUS.4
C5: COLS.7, LDOWN.4, LUP.4
C6: COLS.8, DOWN.4, LEFT.4, LLEFT.4, RIGHT.4, START.4, STOP.4, UP.4
GND: COLS.1, ROWS.1
R0: B4.1, B9.1, F4.1, LLEFT.1, LUP.1, M6.1, MINUS.1, ROWS.2
R1: B6.1, B7.1, F5.1, LDOWN.1, LRIGHT.1, M5.1, ROWS.3, START.1
R2: B5.1, B8.1, F6.1, M4.1, ROWS.4, STOP.1
R3: B3.1, BS.1, F7.1, M3.1, RIGHT.1, ROWS.5
R4: B1.1, F1.1, M2.1, M9.1, ROWS.6, UP.1
R5: B0.1, F2.1, LEFT.1, M1.1, M8.1, ROWS.7
R6: B2.1, DOWN.1, F3.1, M7.1, PLUS.1, ROWS.8
